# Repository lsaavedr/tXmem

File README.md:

# tXmem
teensy3 memory expander

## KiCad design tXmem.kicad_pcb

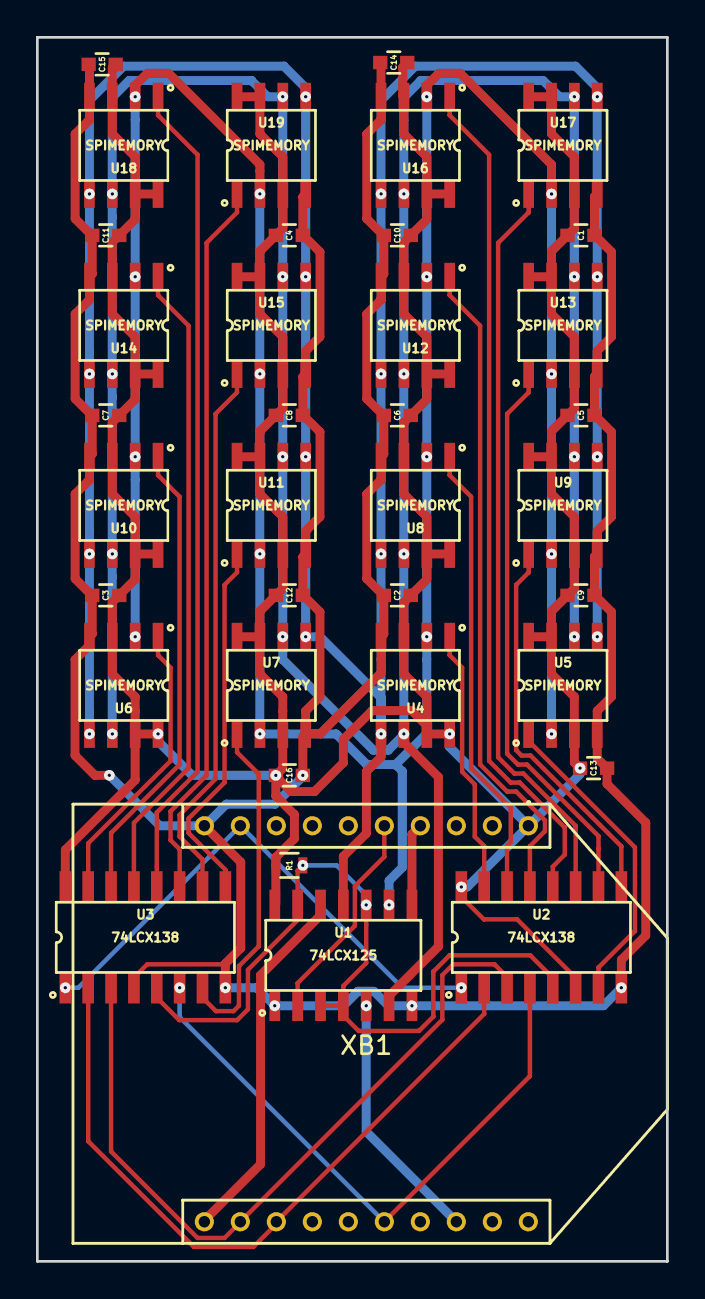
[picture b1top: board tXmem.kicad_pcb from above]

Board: 2 copper layers, 35.0 x 68.0 mm, 37 parts (0 on the bottom side), 30 nets.

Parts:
C1, C2, C3, C4, C5, C6, C7, C8, C9, C10, C11, C12, C13, C14, C15, C16: C104M; C_0603
R1: R103J; R_0603
U1: 74LCX125; SOIC-14
U2, U3: 74LCX138; SOIC-16
U4, U5, U6, U7, U8, U9, U10, U11, U12, U13, U14, U15, U16, U17, U18, U19: SPIMEMORY; SOIC-8
XB1: XBEE; XBee

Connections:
/A0: U2.1, U3.1, XB1.9
/A1: U2.2, U3.2, XB1.13
/A2: U2.3, U3.3, XB1.12
/A3: U2.4, U3.6, XB1.16
/D0: U3.7, U7.1
/D1: U3.9, U11.1
/D2: U3.10, U15.1
/D3: U3.11, U19.1
/D4: U3.12, U18.1
/D5: U3.13, U14.1
/D6: U3.14, U10.1
/D7: U3.15, U6.1
/D8: U2.7, U5.1
/D9: U2.9, U9.1
/D10: U2.10, U13.1
/D11: U2.11, U17.1
/D12: U2.12, U16.1
/D13: U2.13, U12.1
/D14: U2.14, U8.1
/D15: U2.15, U4.1
/MISO: U1.8, XB1.4
/MOSI: U1.12, XB1.11
/SCK: U1.6, U4.6, U5.6, U6.6, U7.6, U8.6, U9.6, U10.6, U11.6, U12.6, U13.6, U14.6, U15.6, U16.6, U17.6, U18.6, U19.6
/SCLK: U1.5, XB1.18
/SI: U1.11, U4.5, U5.5, U6.5, U7.5, U8.5, U9.5, U10.5, U11.5, U12.5, U13.5, U14.5, U15.5, U16.5, U17.5, U18.5, U19.5
/SO: U1.9, U4.2, U5.2, U6.2, U7.2, U8.2, U9.2, U10.2, U11.2, U12.2, U13.2, U14.2, U15.2, U16.2, U17.2, U18.2, U19.2
/~CS: R1.2, U1.3, U1.4, U1.10, U1.13, U2.5, U3.5
/~E: U1.2, XB1.5
GND: C1.2, C2.2, C3.2, C4.2, C5.2, C6.2, C7.2, C8.2, C9.2, C10.2, C11.2, C12.2, C13.2, C14.2, C15.2, C16.2, U1.1, U1.7, U2.8, U3.4, U3.8, U4.4, U5.4, U6.4, U7.4, U8.4, U9.4, U10.4, U11.4, U12.4, U13.4, U14.4, U15.4, U16.4, U17.4, U18.4, U19.4, XB1.10
VCC: C1.1, C2.1, C3.1, C4.1, C5.1, C6.1, C7.1, C8.1, C9.1, C10.1, C11.1, C12.1, C13.1, C14.1, C15.1, C16.1, R1.1, U1.14, U2.6, U2.16, U3.16, U4.3, U4.7, U4.8, U5.3, U5.7, U5.8, U6.3, U6.7, U6.8, U7.3, U7.7, U7.8, U8.3, U8.7, U8.8, U9.3, U9.7, U9.8, U10.3, U10.7, U10.8, U11.3, U11.7, U11.8, U12.3, U12.7, U12.8, U13.3, U13.7, U13.8, U14.3, U14.7, U14.8, U15.3, U15.7, U15.8, U16.3, U16.7, U16.8, U17.3, U17.7, U17.8, U18.3, U18.7, U18.8, U19.3, U19.7, U19.8, XB1.1

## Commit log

2015-08-14 first version!
2015-08-17 work in progress
2015-08-18 dwarfing!
2015-08-23 test fab v1.0
2015-08-23 fix mask clearance and paste clearance
2015-08-23 * usegerberextensions false * via drill from 0.2 to 0.18
2015-09-03 minor fix
